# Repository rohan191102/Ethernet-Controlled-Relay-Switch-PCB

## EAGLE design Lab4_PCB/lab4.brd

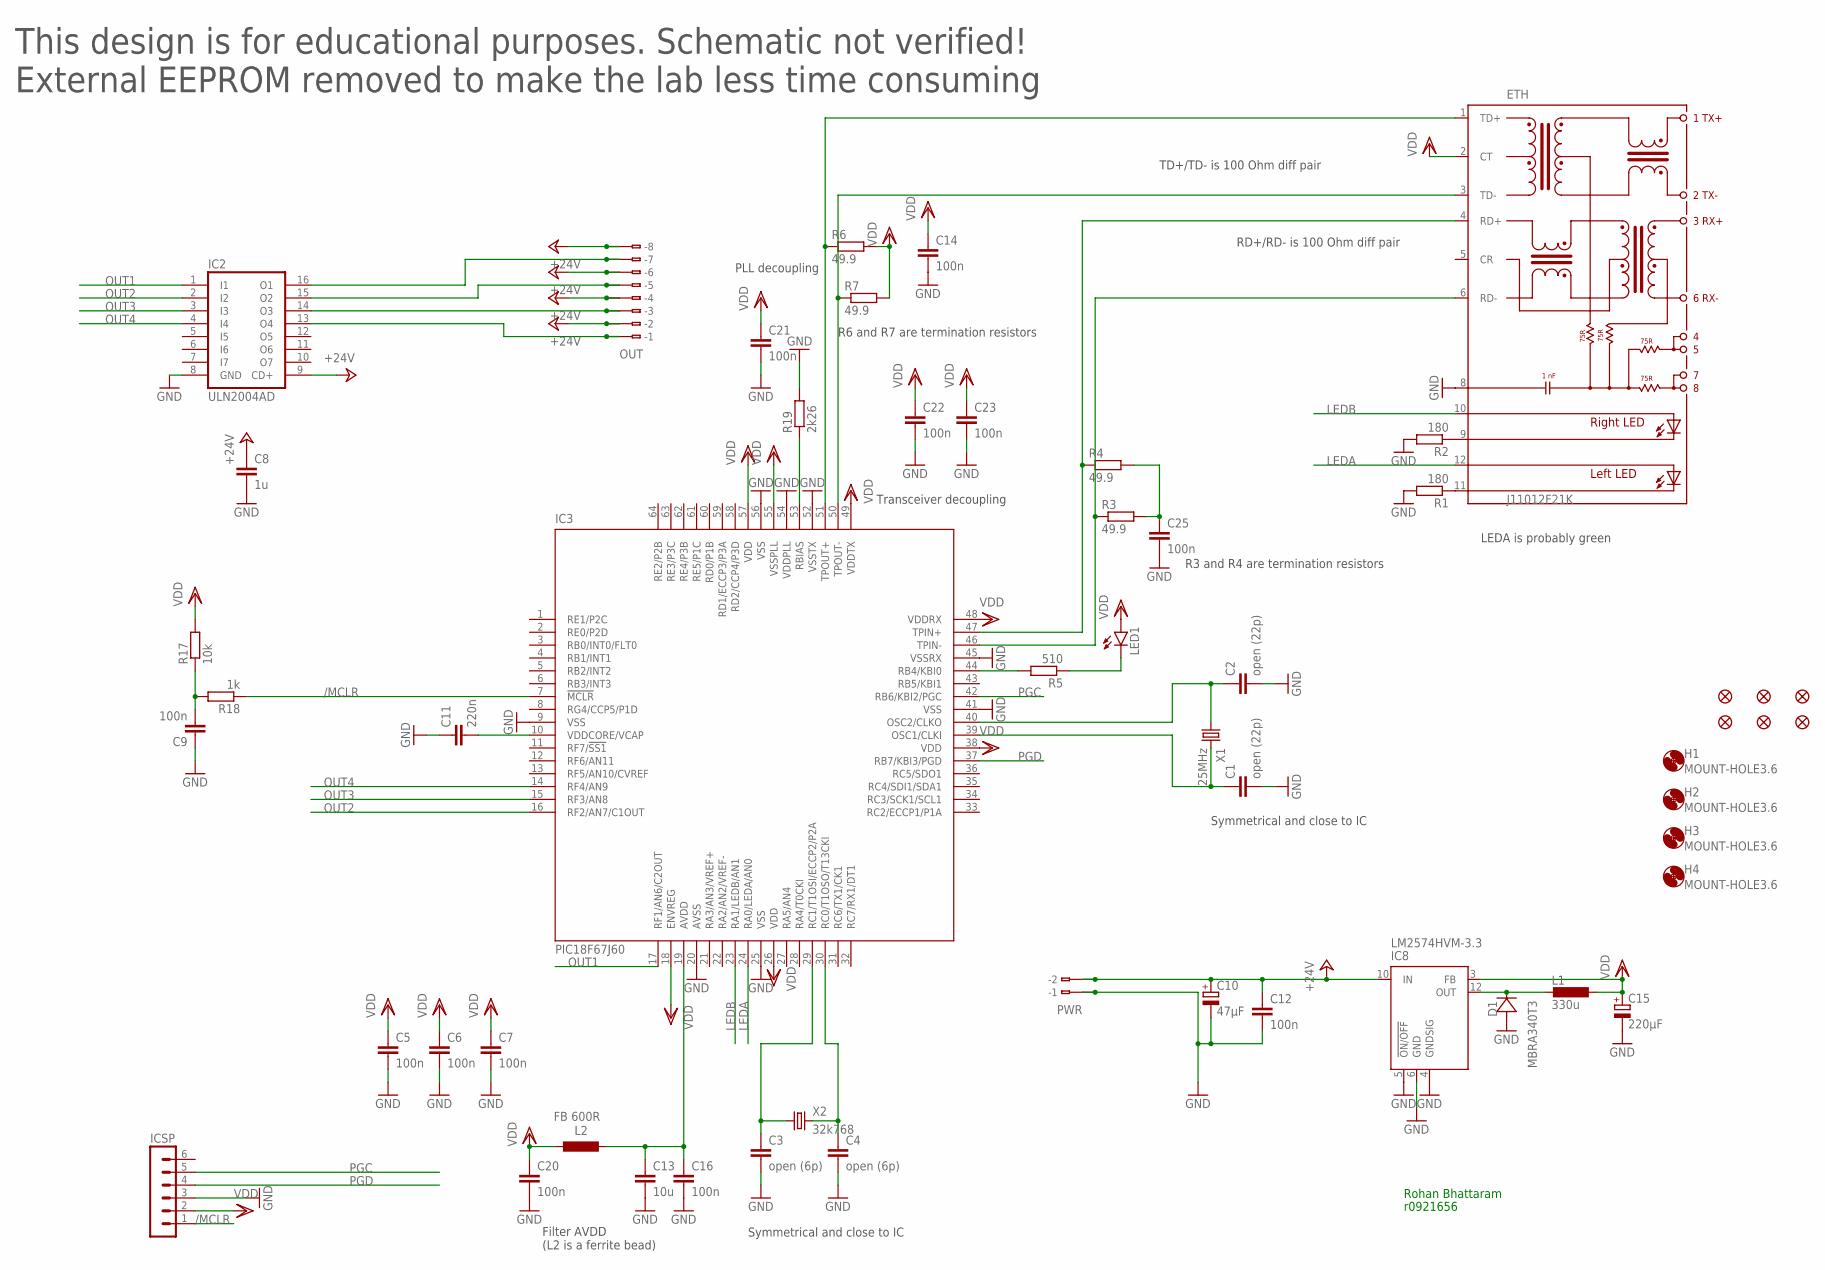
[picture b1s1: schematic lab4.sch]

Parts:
C1, C2: open (22p); C0603
C3, C4: open (6p); C0603
C5, C6, C7, C9, C12, C14, C16, C20, C21, C22, C23, C25: 100n; C0603
C8: 1u; C0603
C10: 47µF; E2,5-5
C11: 220n; C0603
C13: 10u; C0805
C15: 220µF; E2,5-5
D1: MBRA340T3; SMA
ETH: J11012F21K; J1
FID1, FID2, FID3, FID4, FID5, FID6: FIDUCIAL""; FIDUCIAL_1MM
H1, H2, H3, H4: MOUNT-HOLE3.6; 3,6
IC2: ULN2004AD; SO16
IC3: PIC18F67J60; TQFP64-10X10
IC8: LM2574HVM-3.3; SO14W
ICSP: MA06-1
L1: 330u; SRN8040TA
L2: FB 600R; RESC1608X80N
LED1: LEDCHIP-LED0805; CHIP-LED0805
OUT: 233-108
PWR: 233-102
R1, R2: 180; R0603
R3, R4, R6, R7: 49.9; R0603
R5: 510; R0603
R17: 10k; R0603
R18: 1k; R0603
R19: 2k26; R0603
X1: 25MHz; CTS406
X2: 32k768; TC26V

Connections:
+24V: C8.1, C10.+, C12.1, IC2.9 (CD+), IC8.10 (IN), OUT.A2 (-2), OUT.A4 (-4), OUT.A6 (-6), OUT.A8 (-8), OUT.B2 (B-2), OUT.B4 (B-4), OUT.B6 (B-6), OUT.B8 (B-8), PWR.A2 (-2), PWR.B2 (B-2)
/MCLR: IC3.7 (!MCLR), ICSP.1, R18.1
AVDD: C13.1, C16.1, IC3.19 (AVDD), L2.1
GND: C1.2, C2.2, C3.2, C4.2, C5.2, C6.2, C7.2, C8.2, C9.1, C10.-, C11.1, C12.2, C13.2, C14.2, C15.-, C16.2, C20.2, C21.2, C22.2, C23.2, C25.2, D1.A, ETH.8, IC2.8 (GND), IC3.9 (VSS), IC3.20 (AVSS), IC3.25 (VSS), IC3.41 (VSS), IC3.45 (VSSRX), IC3.52 (VSSTX), IC3.54 (VDDPLL), IC3.56 (VSS), IC8.4 (GNDSIG), IC8.5 (!ON/OFF), IC8.6 (GND), ICSP.3, PWR.A1 (-1), PWR.B1 (B-1), R1.2, R2.2, R19.2
LEDA: ETH.12 (A-L), IC3.24 (RA0/LEDA/AN0)
LEDB: ETH.10 (A-R), IC3.23 (RA1/LEDB/AN1)
unnamed: C9.2, R17.1, R18.2
unnamed: IC2.13 (O4), OUT.A1 (-1), OUT.B1 (B-1)
unnamed: IC3.53 (RBIAS), R19.1
unnamed: IC2.14 (O3), OUT.A3 (-3), OUT.B3 (B-3)
unnamed: C4.1, IC3.30 (RC0/T1OSO/T13CKI), X2.2
unnamed: IC2.15 (O2), OUT.A5 (-5), OUT.B5 (B-5)
unnamed: C3.1, IC3.29 (RC1/T1OSI/ECCP2/P2A), X2.1
unnamed: C1.1, IC3.39 (OSC1/CLKI), X1.3 (2)
unnamed: C2.1, IC3.40 (OSC2/CLKO), X1.1
unnamed: C11.2, IC3.10 (VDDCORE/VCAP)
unnamed: IC2.16 (O1), OUT.A7 (-7), OUT.B7 (B-7)
unnamed: ETH.11 (C-L), R1.1
unnamed: ETH.9 (C-R), R2.1
unnamed: C25.1, R3.2, R4.2
unnamed: IC3.44 (RB4/KBI0), R5.2
unnamed: LED1.C, R5.1
OUT1: IC2.1 (I1), IC3.17 (RF1/AN6/C2OUT)
OUT2: IC2.2 (I2), IC3.16 (RF2/AN7/C1OUT)
OUT3: IC2.3 (I3), IC3.15 (RF3/AN8)
OUT4: IC2.4 (I4), IC3.14 (RF4/AN9)
PGC: IC3.42 (RB6/KBI2/PGC), ICSP.5
PGD: IC3.37 (RB7/KBI3/PGD), ICSP.4
R1: ETH.4 (RD+), IC3.47 (TPIN+), R4.1
R2: ETH.6 (RD-), IC3.46 (TPIN-), R3.1
SW: D1.C, IC8.12 (OUT), L1.1
T1: ETH.1 (TD+), IC3.51 (TPOUT+), R6.1
T2: ETH.3 (TD-), IC3.50 (TPOUT-), R7.1
VDD: C5.1, C6.1, C7.1, C14.1, C15.+, C20.1, C21.1, C22.1, C23.1, ETH.2 (CT), IC3.18 (ENVREG), IC3.26 (VDD), IC3.38 (VDD), IC3.48 (VDDRX), IC3.49 (VDDTX), IC3.55 (VSSPLL), IC3.57 (VDD), IC8.3 (FB), ICSP.2, L1.2, L2.2, LED1.A, R6.2, R7.2, R17.2

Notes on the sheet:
Symmetrical and close to IC
PLL decoupling
Transceiver decoupling
LEDA is probably green
This design is for educational purposes. Schematic not verified! External EEPROM removed to make the lab less time consuming
TD+/TD- is 100 Ohm diff pair
RD+/RD- is 100 Ohm diff pair
R3 and R4 are termination resistors
R6 and R7 are termination resistors
Filter AVDD (L2 is a ferrite bead)
Rohan Bhattaram
r0921656

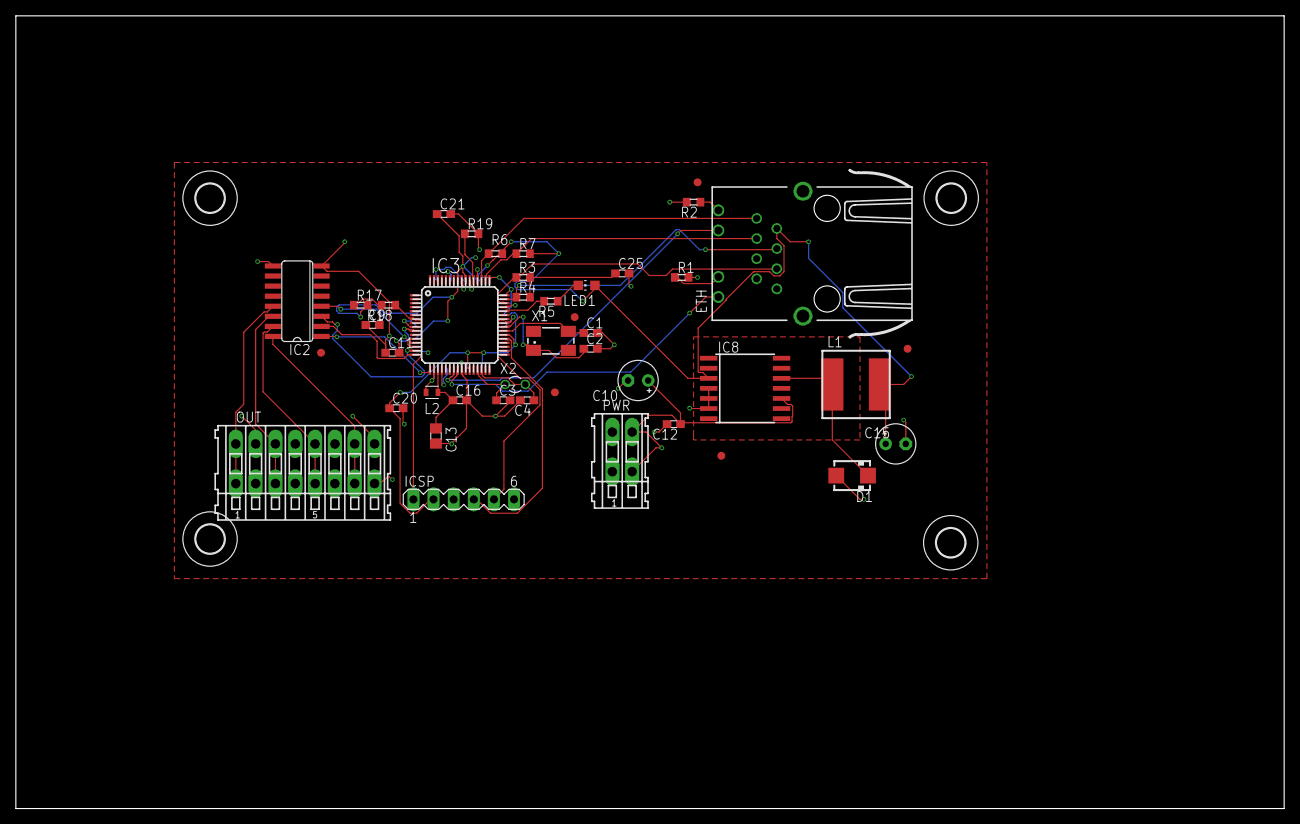
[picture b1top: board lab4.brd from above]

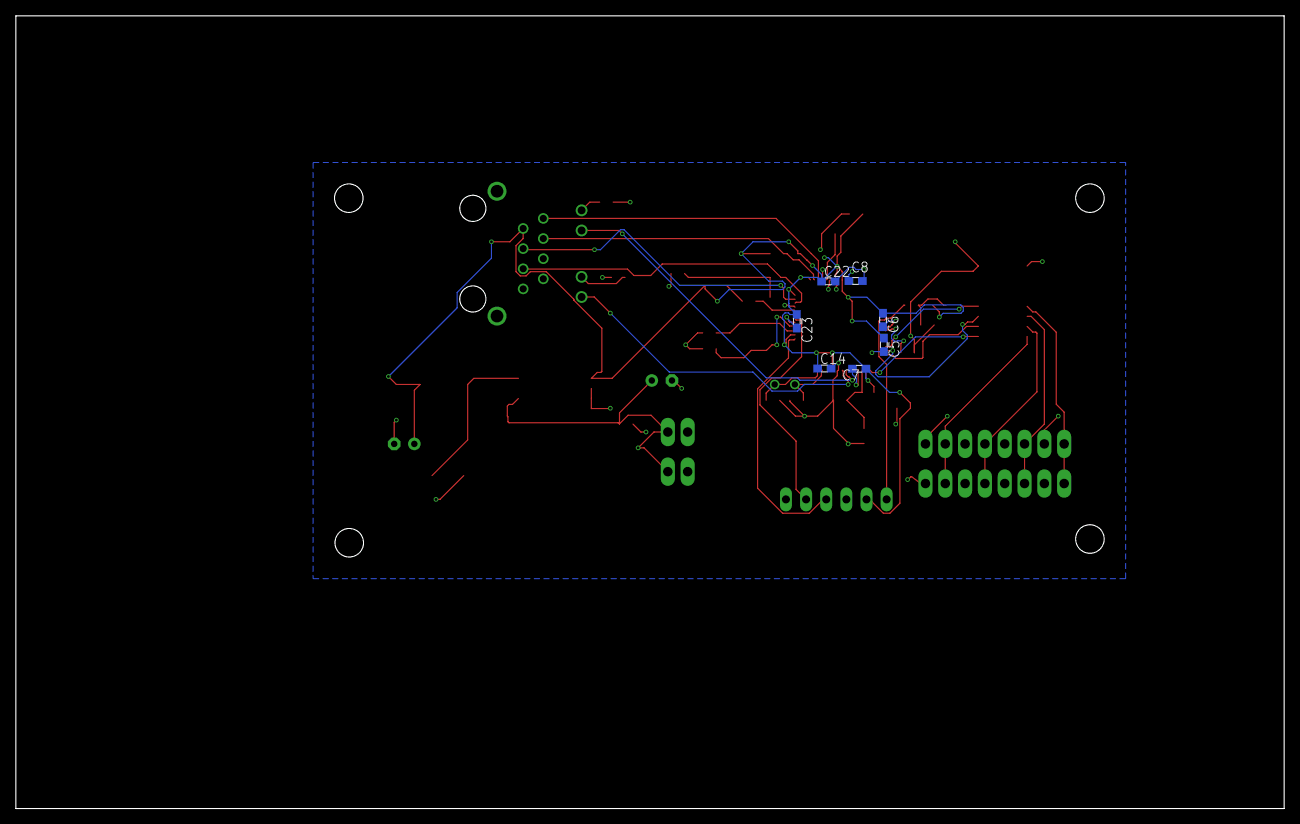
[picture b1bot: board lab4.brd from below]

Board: 4 copper layers, 160.0 x 100.0 mm, 54 parts (7 on the bottom side), 34 nets.

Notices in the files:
parts and their libraries:
microbuilder: This work is placed in the public domain, and may be freely used for commercial and non-commercial work with the following conditions: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
